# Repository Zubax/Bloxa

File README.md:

# Zubax Bloxa

Zubax Bloxa is arguably the most compact practical ESC reference design based on [**Mitochondrik LV**](https://zubax.com/mitochondrik-lv). The key design requirements for Bloxa are:

* compactness;
* low mass;
* low COG;
* compatibility with the [UCANPHY standard](https://forum.opencyphal.org/t/cyphal-can-physical-layer-specification-v1-0/1471).

## Brief specs

* Operating voltage range: **4–8S** Li-ion (LiCoO<sub>2</sub>), 12–34 V
* Continuous power: **200 W**
* Single **Cyphal/CAN** interface
* Software-controllable **5V BEC** output connected to the CAN 5V line
* Aux port available on PCB pads (requires soldering); this port can be used for **RC PWM input** or for connecting the **motor temperature sensor**.
* Dimensions: 36.6x24.9 mm

The main advantage of Bloxa is its miniature size. To achieve it, a novel Mitochondrik mounting technique is used.

Mitochondrik is mounted on the power stage PCB using an intermediary 2 mm thick PCB that serves as a connector.
Soldering is done using the edge connectors on the Mitochondrik, the intermediary  PCB, and the power stage PCB in the plane perpendicular to the PCB planes. 
Also, one of the RF shields on the Mitochondrik needs not be installed (Mitochondrik modules without the RF shield are available upon request, please contact Zubax Robotics).

## Power stage details.

Bloxa power stage uses three BUK9K6R2-40E MOSFET arrays.

| Parameter                                               | Value               |
| :------------------------------------------------------ | ------------------- |
| Drain to Source Voltage (V<sub>ds</sub>)                | 40 V                |
| Current - Continuous Drain (I<sub>d</sub>) @ 25°C       | 40 A                |
| R<sub>ds on</sub> (Max) @ I<sub>d</sub>, V<sub>gs</sub> | 6 mOhm @ 25 A, 10 V |
| Gate Charge (Q<sub>g</sub>) (Max) @ V<sub>gs</sub>      | 35.4 nC @ 10 V      |

The bulk capacitor bank is formed with 3 [180 µF aluminum electrolytic capacitors](https://www.digikey.com/products/en?keywords=565-4066-ND) from [United Chemi-Con](https://www.digikey.com/en/supplier-centers/u/united-chemi-con).

## Release notes

Newest entries at the top.

### Bloxa v1.0

* Hardware over-current protection resistor has been adjusted in accordance with the latest design recommendations. See the [Mitochondrik LV](https://zubax.com/mitochondrik-lv) datasheet for details.
* Current shunts replaced with 3 mohms.

### Bloxa v0.2

* Current shunts replaced (5 mohms replaced with 10 mohms).
* Overcurrent protection added. Itrip is ~35 A.
* RCPWM through-hole connector replaced with smd solder pads.
* Power loss estimations table added to the schematic.
* TVS diode (D1) replaced with one that has lower breakdown voltage.

## License

This project is licensed under the terms of [CC-BY 4.0](https://creativecommons.org/licenses/by/4.0/).

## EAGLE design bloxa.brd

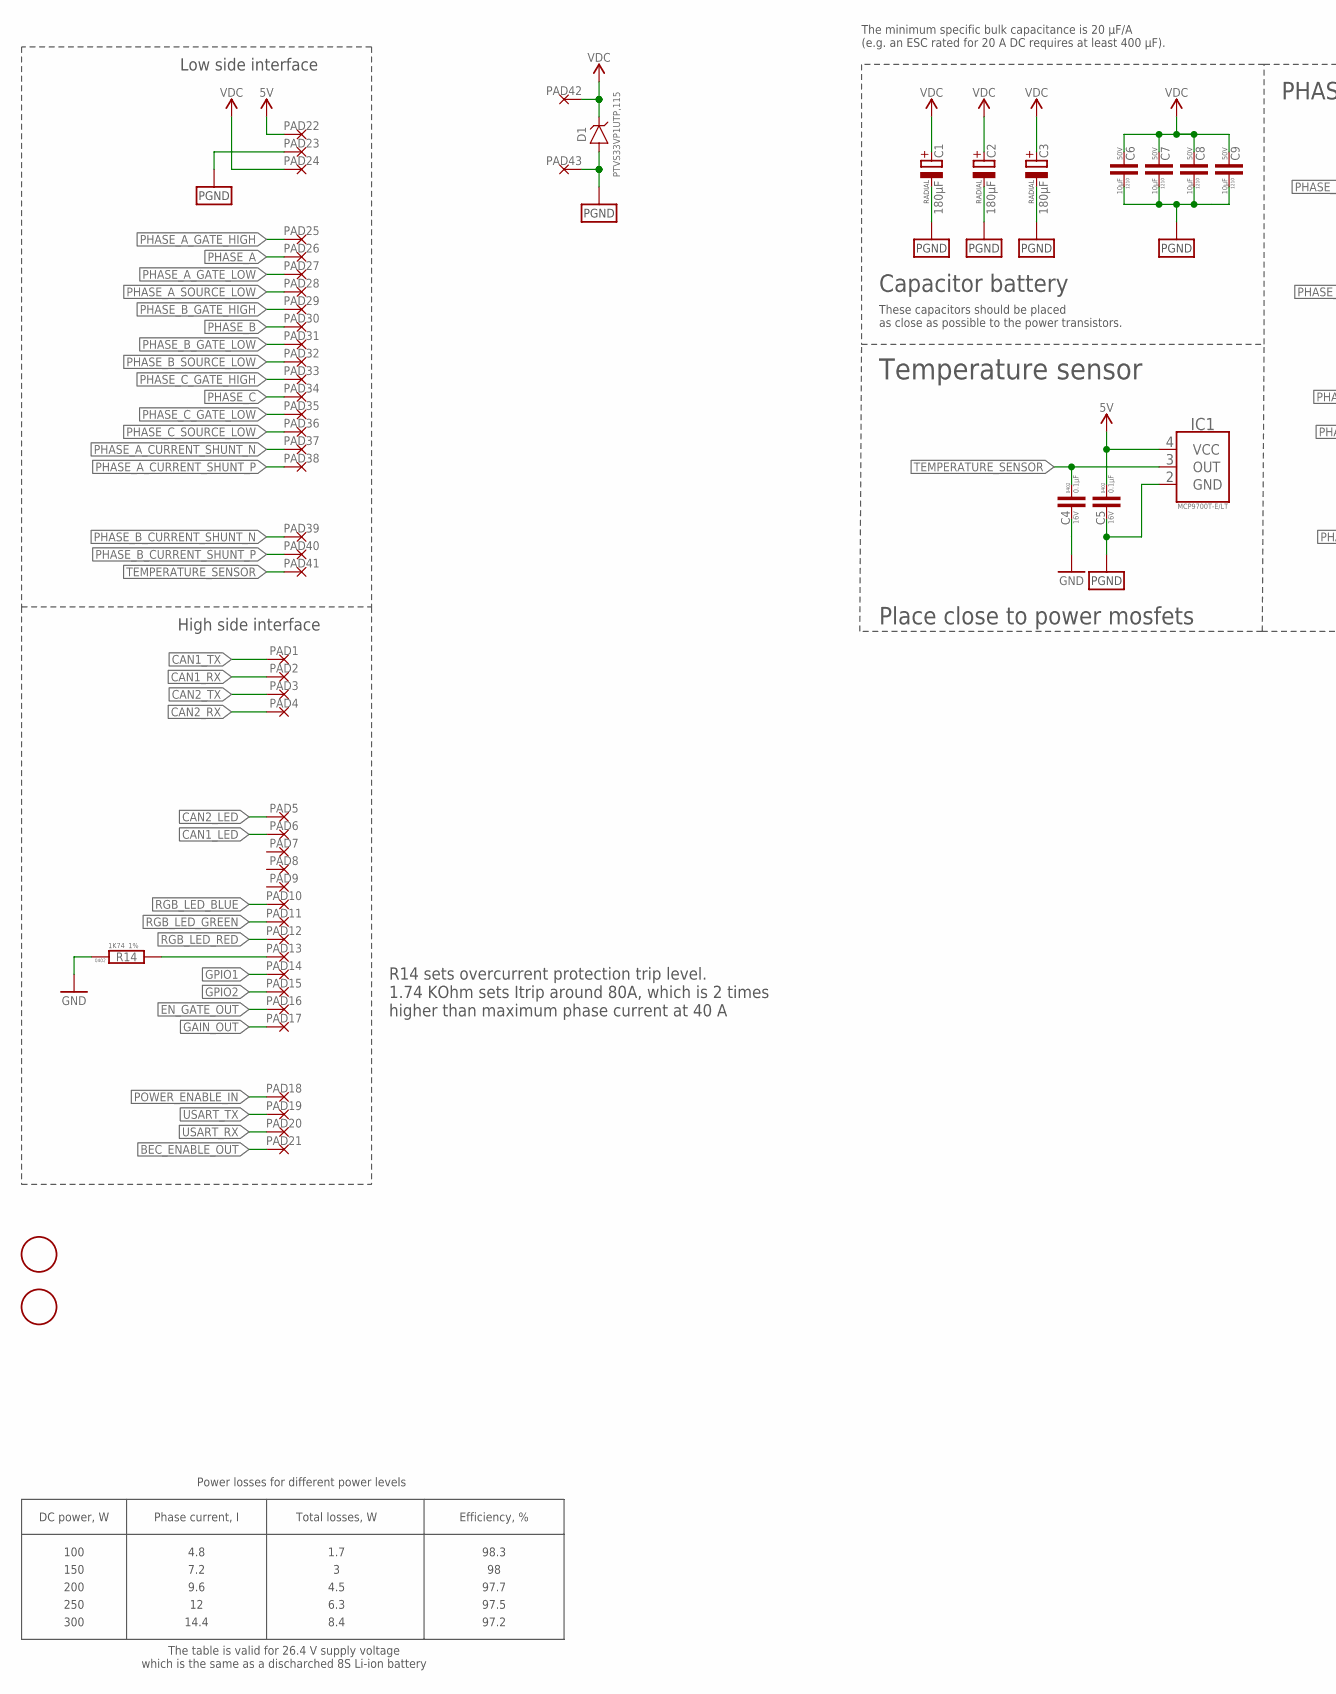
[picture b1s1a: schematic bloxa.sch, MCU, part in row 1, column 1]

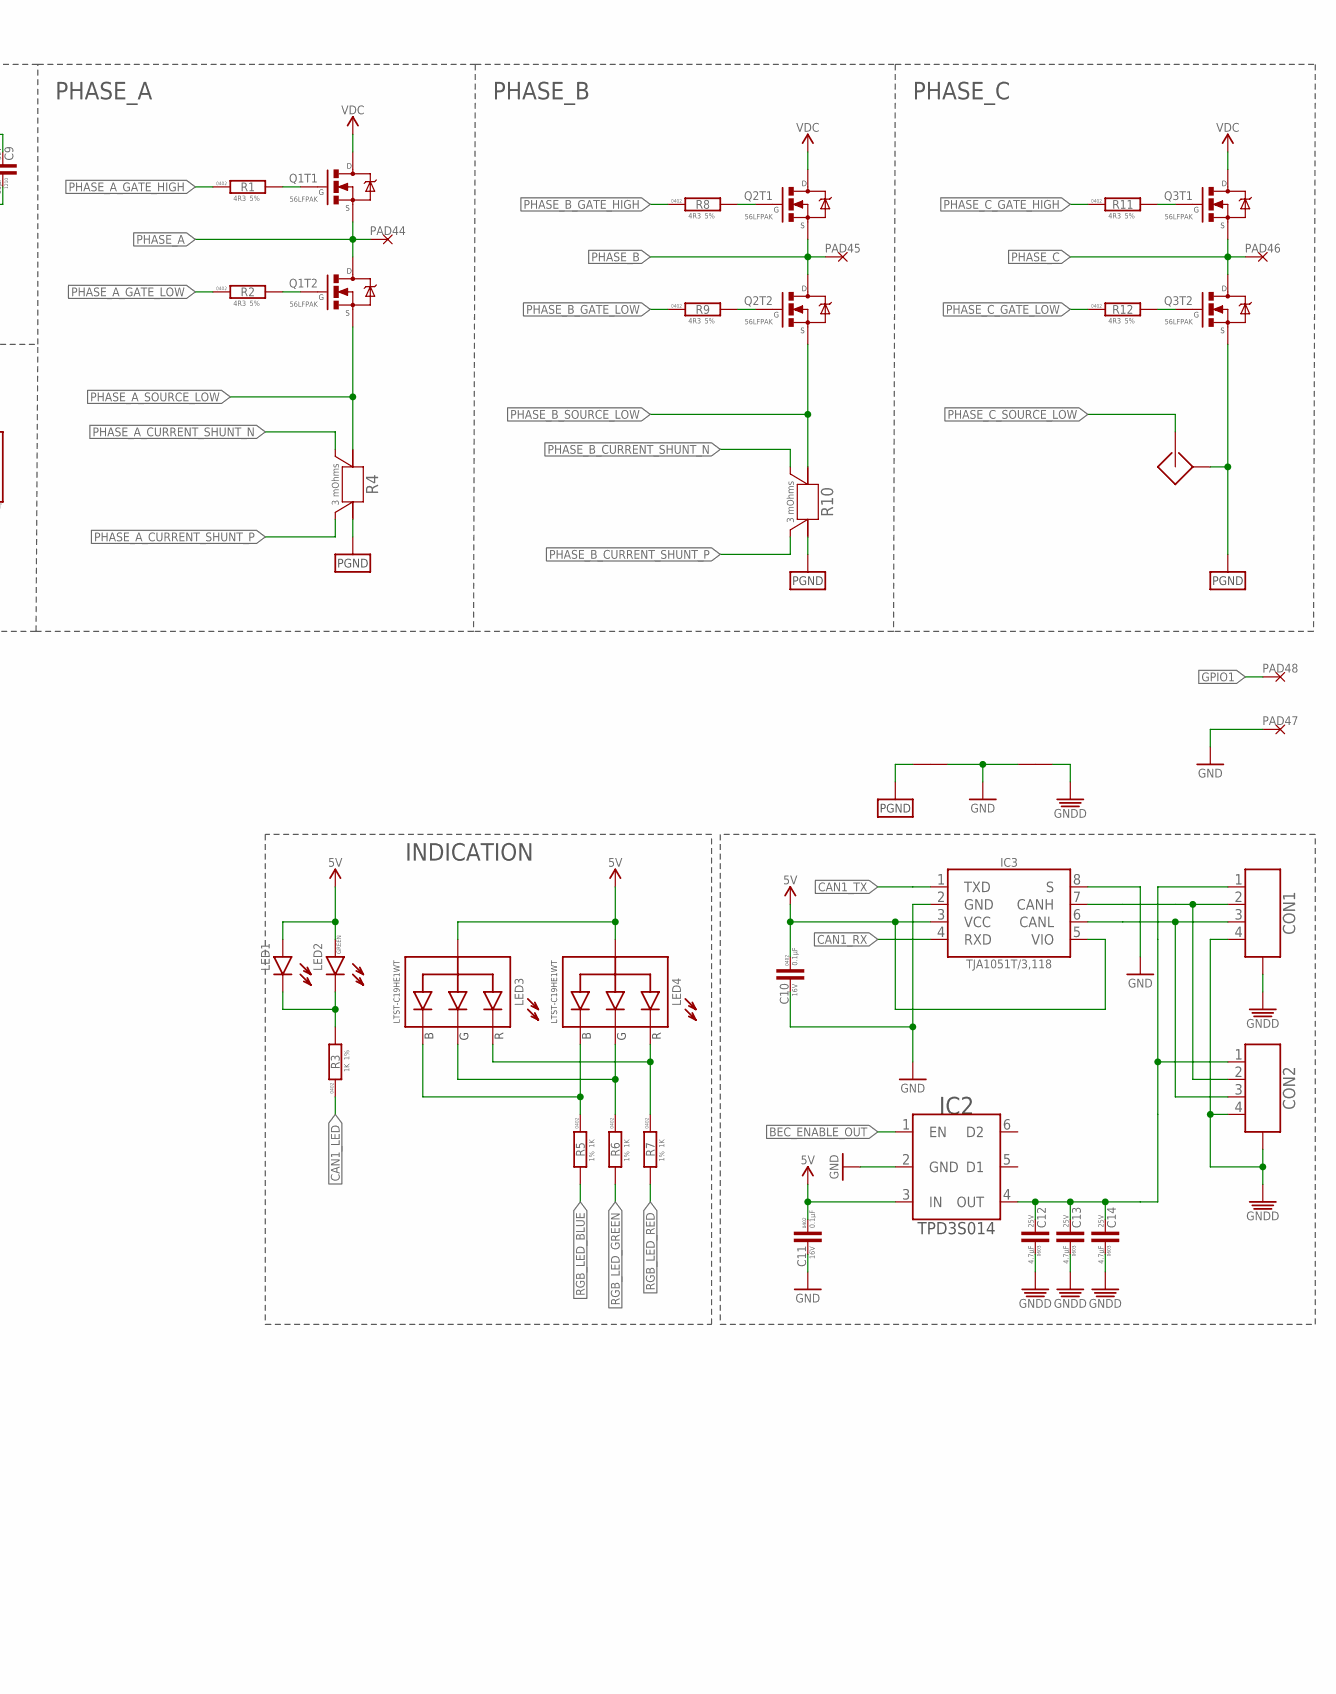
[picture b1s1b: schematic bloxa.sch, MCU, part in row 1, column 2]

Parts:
C1, C2, C3: 180µF; RADIAL_SIDE_8X21.5
C4, C5, C10, C11: 0.1µF; C0402
C6, C7, C8, C9: 10µF; C1210
C12, C13, C14: 4.7µF; C0603
CON1, CON2: CON-4P-JST_GH-RA; JST_GH-4P-RA
D1: PTVS33VP1UTP,115-36V-SOD128; SOD128
FD1, FD2: FIDUCIALMOUNT; FIDUCIA-MOUNT
IC1: MCP9700-SC70-5; SC70-5
IC2: TPD3S014DBVR-SOT23-6; SOT26
IC3: TJA1051(X)/3-SO8; SOIC8
J1, J2: CONNECTION
LED1: GREEN; LED0402
LED2: GREEN; LED0402; DIGIKEY# 1830-IN-S42BT5GCT-ND
LED3, LED4: LTST-C19HE1WT; 0606
PAD1, PAD2, PAD3, PAD4, PAD22, PAD23, PAD24: PAD-1X1.5; SMD_1X1,5
PAD5, PAD6, PAD7, PAD8, PAD9, PAD10, PAD11, PAD12, PAD13, PAD14, PAD15, PAD16, PAD17, PAD18, PAD19, PAD20, PAD21, PAD25, PAD26, PAD27, PAD28, PAD29, PAD30, PAD31, PAD32, PAD33, PAD34, PAD35, PAD36, PAD37, PAD38, PAD39, PAD40, PAD41: PAD-HOLE-0.6; HOLE_0.6
PAD42, PAD43: PAD-4X2; 4X2
PAD44, PAD45, PAD46: PAD-HOLE_1.5; HOLE_1.5
PAD47, PAD48: PAD-S-1.5; 1.5X1.5
Q1, Q2, Q3: BUK9K6R2-40E,115; SOT-1205
R1, R2, R8, R9, R11, R12: 4R3; R0402
R3, R5, R6, R7: 1K; R0402
R4, R10: 3 mOhms; R2512-KELVIN; DIGIKEY# 2019-TLR3APSDTE3L00F50CT-ND
R14: 1K74; R0402; DIGIKEY# 541-1.74KLCT-ND
S1: SENSE; SENSE-0.6

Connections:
BEC_ENABLE_OUT: IC2.1 (EN), PAD21.P$1
CAN1_LED: PAD6.P$1, R3.1
CAN1_RX: IC3.4 (RXD), PAD2.P$1
CAN1_TX: IC3.1 (TXD), PAD1.P$1
CAN1_VDD: C12.P$2 (2), C13.P$2 (2), C14.P$2 (2), CON1.1, CON2.1, IC2.4 (OUT)
CAN2_LED: PAD5.P$1
CAN2_RX: PAD4.P$1
CAN2_TX: PAD3.P$1
EN_GATE_OUT: PAD16.P$1
GAIN_OUT: PAD17.P$1
GND: C4.2, C10.2, C11.2, IC2.2 (GND), IC3.2 (GND), IC3.8 (S), J1.P$1, J2.P$1, PAD47.P$1, R14.1
GNDD: C12.P$1 (1), C13.P$1 (1), C14.P$1 (1), CON1.4, CON1.M$0 (GND), CON1.M$1 (GND), CON2.4, CON2.M$0 (GND), CON2.M$1 (GND), J2.P$2
GPIO1: PAD14.P$1, PAD48.P$1
GPIO2: PAD15.P$1
unnamed: LED3.G, LED4.G, R6.1
unnamed: LED1.C, LED2.C, R3.2
unnamed: CON1.2, CON2.2, IC3.7 (CANH)
unnamed: CON1.3, CON2.3, IC3.6 (CANL)
unnamed: Q1.2 (G), R1.2
unnamed: Q1.4 (G), R2.2
unnamed: Q3.2 (G), R11.2
unnamed: Q3.4 (G), R12.2
unnamed: Q2.2 (G), R8.2
unnamed: Q2.4 (G), R9.2
unnamed: LED3.R, LED4.R, R7.1
unnamed: LED3.B, LED4.B, R5.1
OVERCURRENT_PROTECT_ADJ: PAD13.P$1, R14.2
PGND: C1.-, C2.-, C3.-, C5.2, C6.1, C7.1, C8.1, C9.1, D1.A, IC1.2 (GND), J1.P$2, PAD23.P$1, PAD43.P$1, Q3.3 (S), R4.2, R4.22 (2), R10.2, R10.22 (2), S1.SHELL (SHELLL)
PHASE_A: PAD26.P$1, PAD44.P$1, Q1.1 (S), Q1.5 (D), Q1.6 (D), Q1.EP-5-6 (D)
PHASE_A_CURRENT_SHUNT_N: PAD37.P$1, R4.S1
PHASE_A_CURRENT_SHUNT_P: PAD38.P$1, R4.S2
PHASE_A_GATE_HIGH: PAD25.P$1, R1.1
PHASE_A_GATE_LOW: PAD27.P$1, R2.1
PHASE_A_SOURCE_LOW: PAD28.P$1, Q1.3 (S), R4.1, R4.11 (1)
PHASE_B: PAD30.P$1, PAD45.P$1, Q2.1 (S), Q2.5 (D), Q2.6 (D), Q2.EP-5-6 (D)
PHASE_B_CURRENT_SHUNT_N: PAD39.P$1, R10.S1
PHASE_B_CURRENT_SHUNT_P: PAD40.P$1, R10.S2
PHASE_B_GATE_HIGH: PAD29.P$1, R8.1
PHASE_B_GATE_LOW: PAD31.P$1, R9.1
PHASE_B_SOURCE_LOW: PAD32.P$1, Q2.3 (S), R10.1, R10.11 (1)
PHASE_C: PAD34.P$1, PAD46.P$1, Q3.1 (S), Q3.5 (D), Q3.6 (D), Q3.EP-5-6 (D)
PHASE_C_GATE_HIGH: PAD33.P$1, R11.1
PHASE_C_GATE_LOW: PAD35.P$1, R12.1
PHASE_C_SOURCE_LOW: PAD36.P$1, S1.IN
POWER_ENABLE_IN: PAD18.P$1
RGB_LED_BLUE: PAD10.P$1, R5.2
RGB_LED_GREEN: PAD11.P$1, R6.2
RGB_LED_RED: PAD12.P$1, R7.2
TEMPERATURE_SENSOR: C4.1, IC1.3 (OUT), PAD41.P$1
USART_RX: PAD20.P$1
USART_TX: PAD19.P$1
VDC: C1.+, C2.+, C3.+, C6.2, C7.2, C8.2, C9.2, D1.C, PAD24.P$1, PAD42.P$1, Q1.7 (D), Q1.8 (D), Q1.EP-7-8 (D), Q2.7 (D), Q2.8 (D), Q2.EP-7-8 (D), Q3.7 (D), Q3.8 (D), Q3.EP-7-8 (D)
VDD_5V: C5.1, C10.1, C11.1, IC1.4 (VCC), IC2.3 (IN), IC3.3 (VCC), IC3.5 (VIO), LED1.A, LED2.A, LED3.+ (A), LED4.+ (A), PAD22.P$1

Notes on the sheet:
Low side interface
High side interface
INDICATION
The minimum specific bulk capacitance is 20 μF/A (e.g. an ESC rated for 20 A DC requires at least 400 μF).
PHASE_A
PHASE_B
PHASE_C
Capacitor battery
These capacitors should be placed as close as possible to the power transistors.
Temperature sensor
Place close to power mosfets
DC power, W
Phase current, I
Total losses, W
Efficiency, %
100
150
200
250
300
The table is valid for 26.4 V supply voltage which is the same as a discharched 8S Li-ion battery
4.8
1.7
98.3
7.2
9.6
4.5
97.7
6.3
97.5
14.4
8.4
97.2
Power losses for different power levels
R14 sets overcurrent protection trip level. 1.74 KOhm sets Itrip around 80A, which is 2 times higher than maximum phase current at 40 A

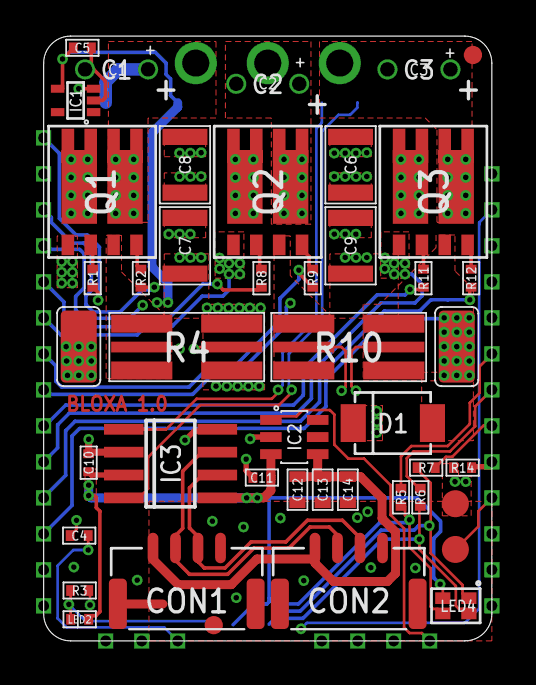
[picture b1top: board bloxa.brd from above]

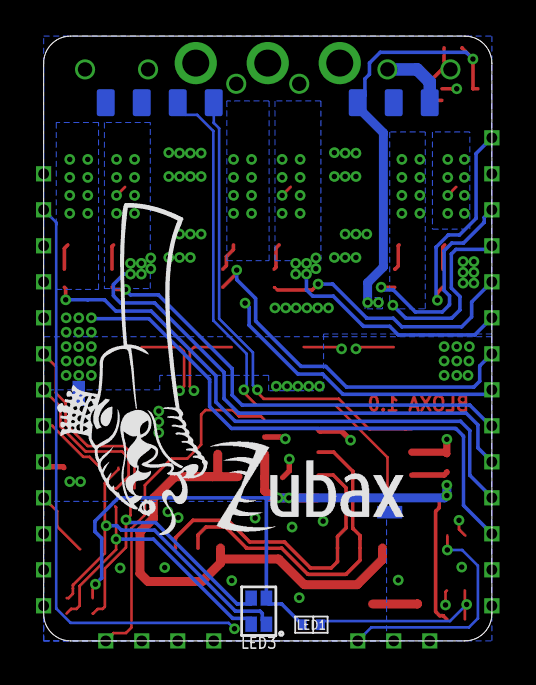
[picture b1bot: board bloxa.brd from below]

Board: 4 copper layers, 24.9 x 33.6 mm, 95 parts (48 on the bottom side), 44 nets.

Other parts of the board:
U$2: DRAGON-18X7
U$13: ZUBAX_LOGO_5X10

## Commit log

2018-12-02 initial import
2018-12-05 proper DRC and some polygons
2018-12-06 more polygones
2018-12-06 some progress
2018-12-06 some more progress
2018-12-10 more polygones updates
2018-12-10 all components moved to top side
2018-12-10 routing complete
2018-12-12 alternate footprints for LED fancy placement
    Will never use it probably
2018-12-13 Renaming
2018-12-13 assembly drawing
2018-12-13 gerber files added
2018-12-17 Added BOM
2019-01-26 OC_ADJ resistor added
2019-02-21 Notes
2019-03-05 Create LICENSE
2019-04-26 3d model import
2019-06-29 cleanup
2019-06-29 tools
2020-02-24 pics for readme
2020-02-26 Revert "Update README.md"
    This reverts commit deaed07196d5ea231de5b75d1a4239a5edf3703c.
2020-02-26 Revert "Revert "Update README.md""
    This reverts commit b39cf6cca478bf70b55c6ae06a6c56247b8d0810.
2020-02-26 Revert "Merge branch 'master' of https://github.com/Zubax/Bloxa"
    This reverts commit b2f1c21598009f83cf69d40fb757bc2455634867, reversing
    changes made to f781607b5a93866d229b0e00b98c93a8223d2532.
2020-02-26 Revert "pics for readme"
    This reverts commit 3b2f7a432af5324931be1961e5be5b0b459c0814.
2020-02-26 readme update
2020-03-30 Bloxa V0.2
    - Current shunts replaced (5 mOhms replaced with 10 mOhms)
    - Overcurrent protection added. Itrip is ~35 A
    - RCPWM th connector replaced with smd solder pads
    - Some design notes added to the schematic
2020-03-30 Some notes
2020-04-03 changelog added as separate sheet to the schematic
2020-04-03 Drawing update
2020-04-03 No more old drawing
2020-04-03 proper drawing
2020-04-03 naming issue
2020-04-03 Pic replacement
2020-06-05 camjob files update
2020-06-05 ERC re-check
2020-06-05 attribute updated
2020-06-05 Revert "Update README.md"
    This reverts commit 57cb23f0877cfcf0b78eeb82708a2c725ba23e2a.
2020-09-02 resolving conflicts
2020-09-02 Hardware files updated
2020-09-02 CAM file for single PCB updated
2020-09-02 Update README.md
    Typo
2020-09-02 Update bloxa.sch
    Typo
2020-09-02 Revert "Update README.md"
    This reverts commit 105605600b114669fe236a7ed24984e5acffa13b.
2023-05-14 change protection resistance
2023-05-20 change Rshunt into 3mOhm
2023-05-21 Remove obsolete changelog and fix the version number on the PCB
